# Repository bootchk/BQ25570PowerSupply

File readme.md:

BQ25570PowerSupply

A breakout board for Texas Instrument's BQ25570 energy harvester, with an additional LDO regulated 3.6V output.

### Overview

The board is a power supply.
It harvests energy, typically from solar cells.
It typically stores energy on a supercapacitor.

The board is designed for nano power applications,
where loads are powered off.
It includes load switches for two power rails.

### Rails

The power rail pins:

    Unregulated storage rail, 0 to 5.5V.  VOUT
    Switched storage rail, 0 to 5.5V      VOUT_SWITCHED
    Regulated MCU power, 1.9 to 3.6V.     VREG
    Switched MCU power, 0 to 3.6V,        VREG_SWITCHED

### Status

Shared at OSHPark.  Minimally tested for design flaws, but not for other performance specs such as leakage.

Needs revision: 

The separate voltage monitor design is flawed.  The Vmon logic output ranges to 5.5V.  It needs a level converter to the same logic levels as the MCU.  In the interim, just don't populate the Vmon.

The LDO might be a SOT-23-6 package, for easier fabrication or choice of regulated voltage.

Obsolete the Good pin output.  Rename the pins.

Test pads.

### Use case

Intended for a nano power application.

The regulated output is for a low power MCU which sleeps mostly.  E.G. a MSP430 that draws 1mA active and say 50nA when sleeping.

The switched regulated output is for low power peripherals, to be powered off when not in use.  E.G. sensors.

The storage rail output pin is normally not used.

The switched storage output is for higher power, higher voltage 5V peripherals, to be powered off when not in use.  E.G. LED's, radios, or motors.

### References

The design follows this:  "Fast-charging a supercapacitor from energy harvesters" 
https://www.edn.com/fast-charging-a-supercapacitor-from-energy-harvesters/
In short, the supercapacitor is on the VOUT pin of the BQ, instead of the VBAT pin.
This makes coldstart relatively short in duration when charging a supercapacitor.

A more typical use of the BQ25570 is to energy harvest to a battery or supercapacitor on the VBAT pin,
then use the buck converter of the BQ25570 to output a higher voltage, say 3.6V.
That design (using a supercapacitor on VBAT) can suffer a long coldstart.
Here, the supercapacitor is on VOUT, and is charged to a high voltage (5.5V)
but adds another LDO to get a regulated 3.6V output.

## Power States and Sequencing

### Coldstart state

Storage is discharged.
The BQ operates in coldstart mode.
It biases the solar cell at 0.6V (not the maximum power point MPT.)
Charging is relatively inefficient.
Voltage on supercapacitor storage remains near zero.

### Warmstart state

Voltage internal to the BQ reaches the VCHGEN voltage of the BQ (1.8V.)
Charging is relatively efficient, biasing the solar cell to its MPT.
The buck converter of the BQ pulses energy to the storage supercap.
Voltage on storage supercap slowly rises from zero.
See more details at the BQ25570 datasheet and the reference above.

VREG and VREG_SWITCHED are off, at 0V.

Ordinarily, in this state you do not use power from the VOUT pin.

### Booted state

Voltage on the storage reaches the programmed Vbat_ok voltage (2.1V.)
The VBAT_OK pin of the BQ asserts high and enables the LDO.
The LDO begins operation in the linear mode, yielding  more than 2.0V (after subtracting Vdo of the regulator, less than 0.1 V.) 

Any MCU on the VREG pin powers on (boots, from a power on reset.)
It should almost immediately go back to sleep until storage and voltage increase.
There is hysteresis.
The BQ will assert its VBAT_OK pin
at a slightly higher voltage (Vbat_ok_hyst) than the voltage (Vbat_ok) at which it deasserts VBAT_OK.
So there is 0.1V on the capacitor to carry the MCU through booting.

Voltage on storage, VOut, and VReg will continue to rise.

The MCU can read its own Vcc voltage to know when the system is in this state.
The MCU can read its own Vcc voltage to know when it is nearing brownout.

The MCU boots at rising voltage Vsys+ (1.99V max) but will not brownout reset until falling voltage Vsys- 1.7V.

### Regulation state

Voltage on the storage reaches the set point of the LDO (3.6V.)
The LDO regulates (limits) voltage on VReg to 3.6V.
The MCU Vmax is 3.6V.

Voltage on storage continues to rise.
Additional voltage and energy on storage is "reserve."

The MCU can read its own Vcc to know when the system is in this state
(when Vcc is near 3.6V.)
The MCU can control energy use according to its own Vcc.
For example, the MCU can switch on high-power peripherals
only in this state.
Or it can use high-power peripherals down to a Vcc voltage between 2 V and 3.6 V.

### Full

Voltage on storage is the max that the BQ will provide, 5.5V.
The supercap must be rated for this voltage.

The MCU cannot know how much excess voltage is on storage.
The MCU can only know that if its Vcc is near 3.6V, there might be excess voltage on storage.

## Pinout

    Sol1           Voltage in, positive terminal of solar cell
    GND            Negative terminal of solar cell

    Supercap1      Positive terminal of storage supercapacitor
    GND            Negative terminal of supercap

    VOut           Unregulated storage rail, 0 to 5.5V.  Same net as Supercap1.
    VOutSw         Switched storage rail, 0 to 5.5V
    OutSw          Logic input, high to switch VOutSw.
     
    VReg           Regulated MCU power, 2.0 to 3.6V.     
    VRegSw         Switched MCU power, 0 to 3.6V,   
    RegSw          Logic input, high to switch VRegSw     

    Good           Logic output, high when VReg is > 2.0V.  Same net as BQ VBAT_OK.

## Programming 

### Programming the BQ 25570

Many voltages cited above are due to the programming of the BQ25570.

The programming can be changed by choosing resistors in the programming nets.

These are the voltages for the BQ programming resistors in the design (in the bill of materials.)

    V_OV          The overflow voltage of the BQ boost charger     5.5V (the max the BQ will output)

    VOUT          The regulated voltage of the BQ buck converter   5.5V

    V_BAT_OK_HYST The rising voltage at which VBatOk asserts       2.1V
    V_BAT_OK_     The falling voltage at which VBatOk deasserts    2.0V

(The undervoltage of the BQ is hardwired in the BQ.)

Again note that the BQ buck converter/regulator is not used in the usual fashion,
but to charge the supercapacitor.

### Programming the LDO

The regulated voltage of the LDO is determined by the part number of the LDO.
(Set at the factory.)

## Programming for the MSP430

The BQ is programmed with the MSP430 in mind.
Since the MCU is on the LDO output rail (VReg), and the LDO has a voltage drop Vdo of about 0.1V at 1mA,
the voltages programmed for the BQ V_BAT_OK are 0.1V higher than the voltages the MCU sees.

(The MSP430 in LPM4.5 sleep is essentially powered off and reset,
but GPIO pins are monitored for interrupts that wake.
Waking from LPM4.5 is mostly the same as a power on reset,
except a flag tells you it is from sleep.
The MSP430FR family has FRAM to maintain SW state,
so a reset from sleep can easily recover state.)

### Boot voltage

The BQ asserts Vbat_ok signal at 2.1V, when MCU sees 2.0.
This is greater than the the MSP430 Vsys+ (1.99V max) , the voltage at which the MSP430 is guaranteed to boot (come out of reset.)

### Reset voltage

Furthermore, this board is designed to allow the MSP430 to enter its very lowest power state.
That state is LPM4.5 with SVS shut down ( a substate of LPM4.5,) drawing only 16nA.

The SVS is the system voltage monitor that can help ensure proper reset.
In the mode with SVS disabled, the MSP430 draws less current.
But disabling SVS requires careful consideration of brownout reset requirements.

The requirements for a safe reset when SVS is disabled:
(from the MSP430 datasheet) 

    Vcc less than Vbor (0.1V)
    Vcc greater than Vbor for time tBOR_safe (10 mS)

If these requirements are not met and SVS is disabled, the MSP is not guaranteed to come out of reset after a voltage drop.

In summary, in this design, the BQ25570 signal Vbat_ok cycles (switches on and off)
power (the LDO) to the MSP430 MCU,
so as to meet the above requirements.

When Vbat_ok goes low at level VBAT_OK (2.0V) , the LDO is disabled.
Voltage and current from the LDO drops to zero.
As it drops below MSP Vsys- (1.7V min),
the MSP enters the reset state, drawing 50uA.

Typical filter capacitors on the MCU are 10uF.
At 50uA current, the filter caps discharge in less than a millisecond.
Thus voltage on the MSP Vcc pin quickly drops below MSP Vbor of 0.1V.

The other requirement is to stay in this condition (Vcc less than 0.1V) for time tBOR_safe.
Since voltage on the supercap is at level VBAT_OK (2.0V)
the voltage must rise to level VBAT_OK_HYST (2.1V)
before the BQ raises Vbat_ok again and enables the LDO.

As an example, assuming a 1F supercap and 3mW from the solar cell (say a Powerfilm LR3-200-37 at 1000 lux)
it takes 0.2 seconds to charge the supercap from 2.0 to 2.1V.
Said time is greater than the requirement.
Other choices ( using a smaller supercap and larger solar cell)
must consider the same requirements.

## Max current ratings

    VReg          LDO             (TI part TSP7A02)            200 mA

    VOutSwitched  LoadswitchOut   (TI part number TPS27081A)     3 A
    
    VRegSwitched  LoadswitchReg   (TI part number TPS22860)    200 mA

## Recommmended operating conditions and LDO dropout

The recommended load on VREG is only a few mA.
The recommended load is very much less than the rated load of the parts.
An MSP430 MCU at 1 Mhz uses only 1mA.

The voltage seen on the VREG net depends on the dropout voltage of the LDO (Vdo)
which depends on load current.

For conditions:

    - temperature -40 to +85 degrees C
    - current 1 mA
    - voltage out 3.6V

the LDO datasheet shows typical Vdo of 0.08V.

The programming of the BQ Vbat_ok signal 
and the choice of MCU depends on such a small Vdo of say 0.1V.

If the MCU on VREG and peripherals on VREG_SW use much more power than say 10's of mA,
you should consider the effect on LDO dropout,
and not switch the peripherals unless Vreg is higher than say 2.3V as determined by the MCU.
Pulling a higher load might increase the Vdo and lower the voltage seen by the MCU,
possibly enough to brown it out.

## Pullups/Pulldowns on signals

The board has a pullup resistor RVoutPull on LoadswitchOut (TI part number TPS27081A).
Note this is per the example for standby power in the LS datasheet.
The pullup is NOT on the enable input, but to between the mosfets on the load switch.
This pullup keeps the loadswitch off while voltage is rising.

The board has no pullup or pulldown on the enable of LoadswitchReg   (TI part number TPS22860).
The loadswitch is on the same rail VReg as the MCU, switched by the MCU.
The MCU should early on set the enable low, and set it high only momentarily.

The LDO has a "Smart enable" feature to ensure it is shutdown during power up.

## Quiescent current of the power supply

Quiescent current is the current out of storage when any attached load is not drawing current.
Quiescent current subtracts from any charging current (say from the solar cell.)

The storage leaks when being charged and also self discharges when not being charged.
Typically this current dominates.
Typically this current is on the order of 1 uA (microamps).
This current depends on the capacitance in F among other things like the supercap technology.
I exclude this current from quiescent current.
But the solar cell current must provide this current to keep storage charged.

### Before LDO enabled (Vbat_ok signal low)

The MCU is not booted so doesn't drive the loadswitch enable pins.

    LoadswitchOut is shutdown(standby)     50 nA
    LoadswitchReg is not powered            0 nA
    LDO is shutdown                         3 nA

    total                                  50 nA

LoadswitchOut has a feature "Smart Enable" to ensure it is not enabled on voltage rising during powerup.

### After LDO enabled (booted state)

The MCU is booted (which is a load) but sleeping mostly, and holding load switches off.

    LoadswitchOut is standby               50 nA
    LoadswitchReg is powered but shutdown  12 nA
    LDO is enabled                         25 nA
    MCU is booted but in low power mode    50 nA

    total                                 137 nA

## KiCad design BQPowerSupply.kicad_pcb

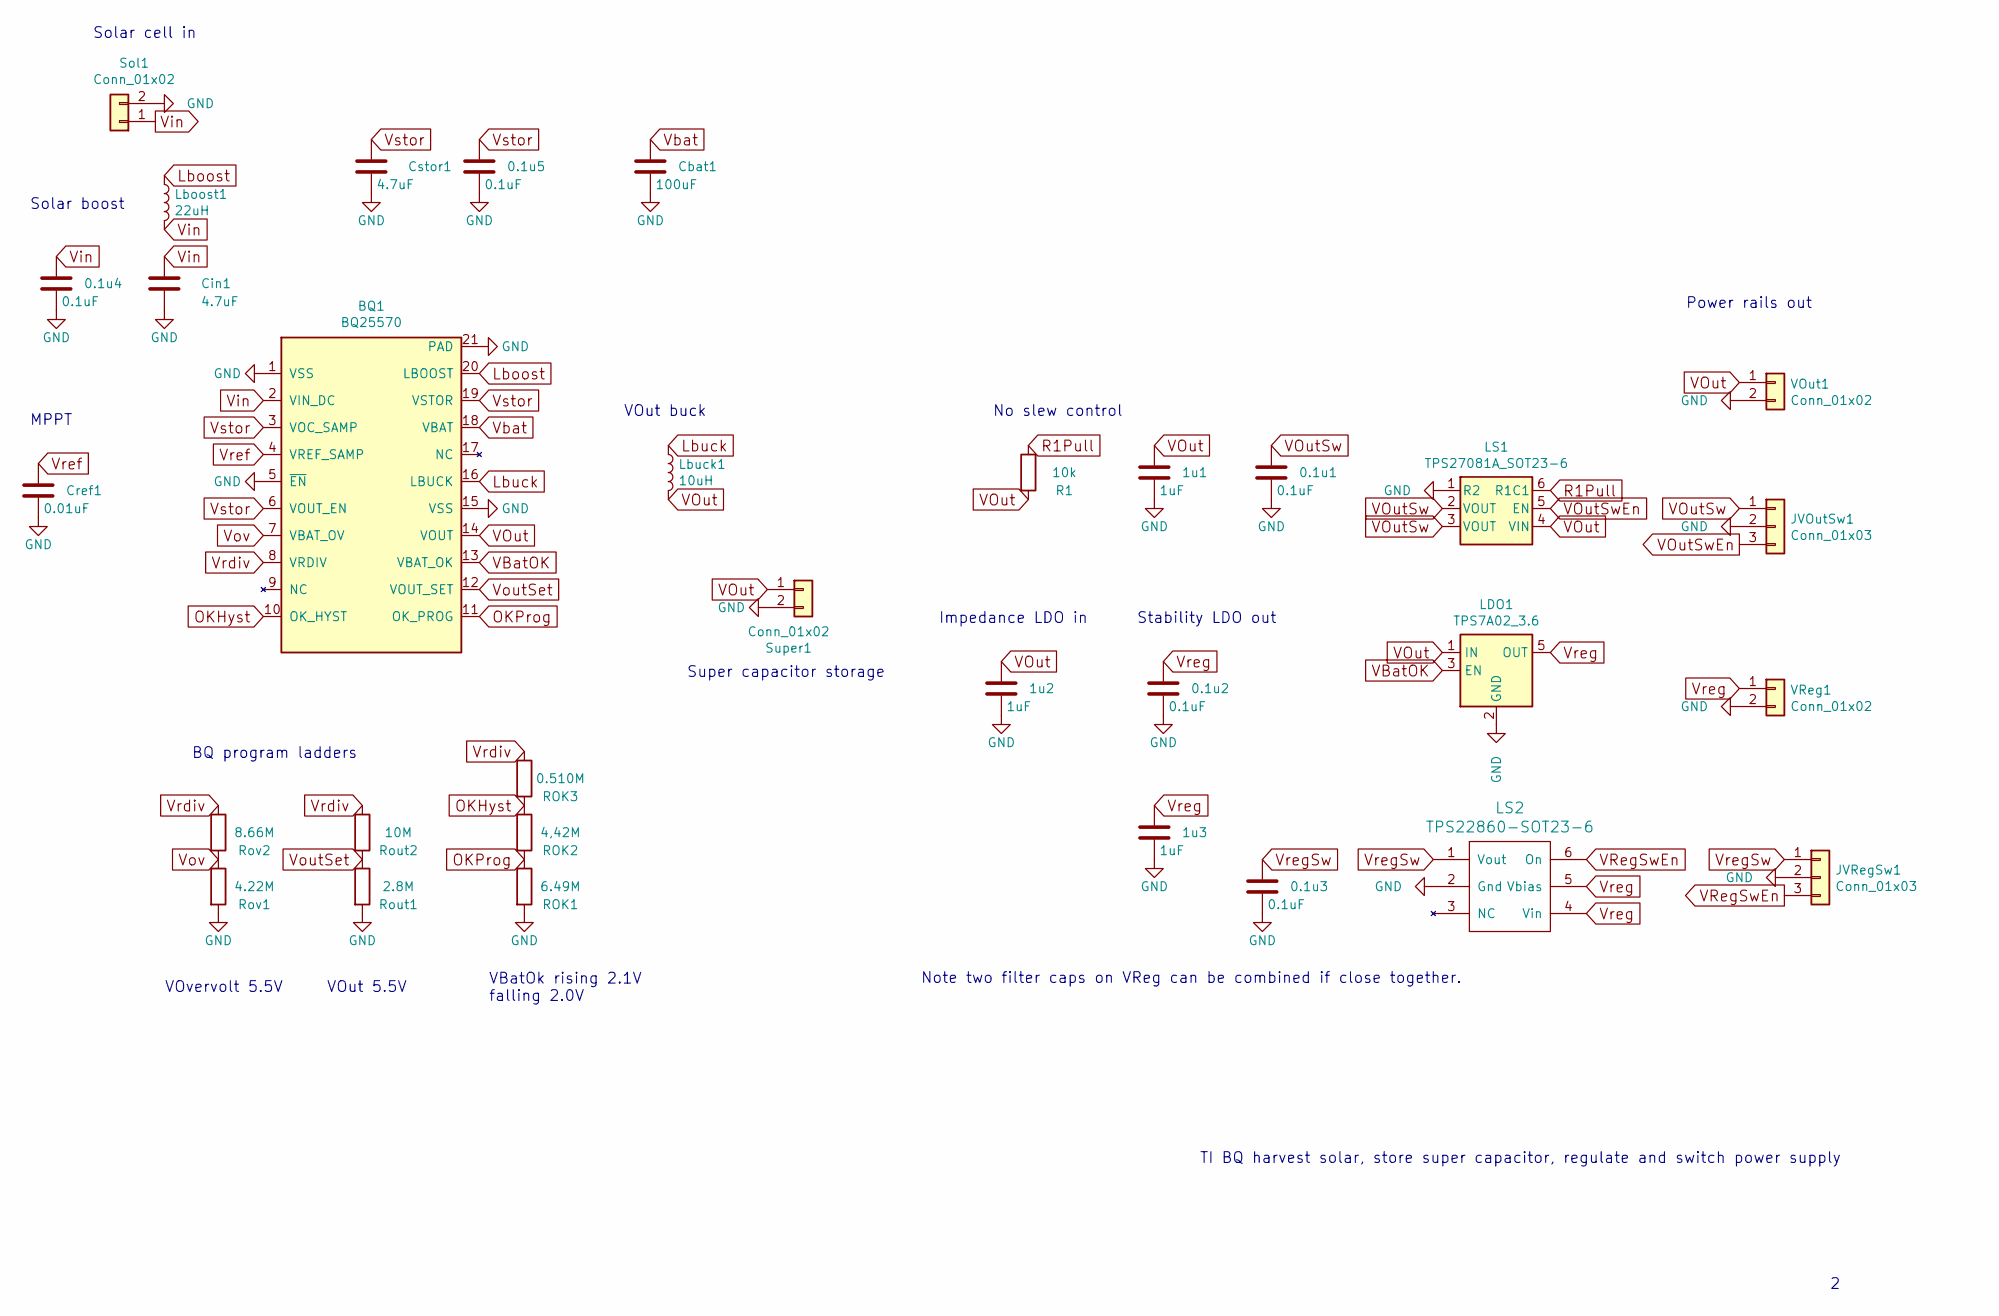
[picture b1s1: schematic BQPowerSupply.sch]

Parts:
0.1u1, 0.1u2, 0.1u3, 0.1u4, 0.1u5: 0.1uF; C_0603_1608Metric
1u1, 1u2, 1u3: 1uF; C_0603_1608Metric
BQ1: BQ25570; QFN-20-1EP_3.5x3.5mm_P0.5mm_EP2x2mm_ThermalVias
Cbat1: 100uF; C_1206_3216Metric
Cin1: 4.7uF; C_0805_2012Metric
Cref1: 0.01uF; C_0603_1608Metric
Cstor1: 4.7uF; C_0805_2012Metric
JVOutSw1: Conn_01x03; PinHeader_1x03_P2.54mm_Vertical
JVRegSw1: Conn_01x03; PinHeader_1x03_P2.54mm_Vertical
LDO1: TPS7A02_3.6; SOT-23-5
LS1: TPS27081A_SOT23-6; SOT-23-6
LS2: TPS22860-SOT23-6; SOT-23-6
Lboost1: 22uH; Wurth2828
Lbuck1: 10uH; Wurth2828
R1: 10k; R_0603_1608Metric
ROK1: 6.49M; R_0603_1608Metric
ROK2: 4,42M; R_0603_1608Metric
ROK3: 0.510M; R_0603_1608Metric
Rout1: 2.8M; R_0603_1608Metric
Rout2: 10M; R_0603_1608Metric
Rov1: 4.22M; R_0603_1608Metric
Rov2: 8.66M; R_0603_1608Metric
Sol1: Conn_01x02; PinHeader_1x02_P2.54mm_Vertical
Super1: Conn_01x02; PinHeader_1x02_P2.54mm_Vertical
VOut1: Conn_01x02; PinHeader_1x02_P2.54mm_Vertical
VReg1: Conn_01x02; PinHeader_1x02_P2.54mm_Vertical

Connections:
GND: 0.1u1.2, 0.1u2.2, 0.1u3.2, 0.1u4.2, 0.1u5.2, 1u1.2, 1u2.2, 1u3.2, BQ1.1 (VSS), BQ1.5 (~EN), BQ1.15 (VSS), BQ1.21 (PAD), Cbat1.2, Cin1.2, Cref1.2, Cstor1.2, JVOutSw1.2, JVRegSw1.2, LDO1.2 (GND), LS1.1 (R2), LS2.2 (Gnd), ROK1.2, Rout1.2, Rov1.2, Sol1.2, Super1.2, VOut1.2, VReg1.2
Lboost: BQ1.20 (LBOOST), Lboost1.1
Lbuck: BQ1.16 (LBUCK), Lbuck1.1
OKHyst: BQ1.10 (OK_HYST), ROK2.1, ROK3.2
OKProg: BQ1.11 (OK_PROG), ROK1.1, ROK2.2
R1Pull: LS1.6 (R1C1), R1.1
VBatOK: BQ1.13 (VBAT_OK), LDO1.3 (EN)
VOut: 1u1.1, 1u2.1, BQ1.14 (VOUT), LDO1.1 (IN), LS1.4 (VIN), Lbuck1.2, R1.2, Super1.1, VOut1.1
VOutSw: 0.1u1.1, JVOutSw1.1, LS1.2 (VOUT), LS1.3 (VOUT)
VOutSwEn: JVOutSw1.3, LS1.5 (EN)
VRegSwEn: JVRegSw1.3, LS2.6 (On)
Vbat: BQ1.18 (VBAT), Cbat1.1
Vin: 0.1u4.1, BQ1.2 (VIN_DC), Cin1.1, Lboost1.2, Sol1.1
VoutSet: BQ1.12 (VOUT_SET), Rout1.1, Rout2.2
Vov: BQ1.7 (VBAT_OV), Rov1.1, Rov2.2
Vrdiv: BQ1.8 (VRDIV), ROK3.1, Rout2.1, Rov2.1
Vref: BQ1.4 (VREF_SAMP), Cref1.1
Vreg: 0.1u2.1, 1u3.1, LDO1.5 (OUT), LS2.4 (Vin), LS2.5 (Vbias), VReg1.1
VregSw: 0.1u3.1, JVRegSw1.1, LS2.1 (Vout)
Vstor: 0.1u5.1, BQ1.3 (VOC_SAMP), BQ1.6 (VOUT_EN), BQ1.19 (VSTOR), Cstor1.1

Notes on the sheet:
TI BQ harvest solar, store super capacitor, regulate and switch power supply
VOut buck
MPPT
Solar boost
VOut 5.5V
BQ program ladders
VOvervolt 5.5V
VBatOk rising 2.1V falling 2.0V
Power rails out
No slew control
Impedance LDO in
Stability LDO out
Note two filter caps on VReg can be combined if close together.
Super capacitor storage
Solar cell in

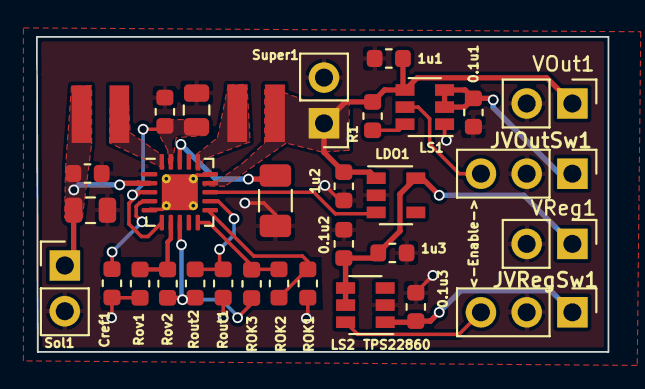
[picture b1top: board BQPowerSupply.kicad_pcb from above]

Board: 2 copper layers, 31.8 x 17.5 mm, 32 parts (0 on the bottom side), 20 nets.

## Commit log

2022-04-08 Update readme.md
    Describe typical use of BQ25570, how this design differs.
2022-04-09 Rev 2 without voltage monitor, with SOT23-5 for LDO
